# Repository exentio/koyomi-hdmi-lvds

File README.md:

# Project Koyomi - HDMI-LVDS adapter

This is part of the development of Project Koyomi, read [this blog post](https://blog.exentio.sexy/2023/12/11/project-koyomi-planning.html)
for more.  
The purpose of this adapter is to test and play around with the display of the
Vaio P before further development of the motherboard and to be used in
hand-wired builds.  

**⚠️ WARNING: at the moment of writing, the board hasn't been tested.**  

The board uses Texas Instruments' SN75LVDS83B LVDS transmitter and TFP401 DVI
receiver to send video out to the display.  

The display connector is made by I-PEX, and the model numbers are
`20374-030E-31`/`20374-R30E-31`, they're the same but the 0 variant seems to be
more common.  
The display, in my case a LT080EE04100 by Toshiba (it should be the same for
all Vaio Ps), has no backlight driver, and for that the backlight pins are
broken out, allowing testing of different drivers.  

Reference timings from [this post on patters' blog](https://pcloadletter.co.uk/2012/07/06/iemgd-for-vaio-p/),
huge thank you!  

Pixel clock in Hz: `83600000`  
Horizontal active pixels: `1600`  
Horizontal front porch: `32`  
Horizontal sync time: `65`  
Horizontal back porch: `97`  
Horizontal blank time (HFP+HST+HBP): `194`  
Vertical active pixels: `768`  
Vertical front porch: `1`  
Vertical sync time: `1`  
Vertical back porch: `8`  
Vertical blank time (VFP+VST+VBP): `10`  

---

### Forking guidelines
I hope that this design will inspire people to work on similar projects, and
that they'll be used as references to learn how to work on similar projects!  
If you want to make any contribution, you're welcome to fork and send a pull
request, as long as LLMs are not directly involved and you understand your
changes: please refer to (HUMAN.md)[https://github.com/exentio/koyomi-hdmi-lvds/blob/main/HUMAN.md], thank you.  

You're also welcome to make changes to any part of this project to implement
different design choices, without having to send a pull request; however, if
your fork takes a completely different direction from Koyomi and breaks
compatibility, I kindly ask you to drop the name "Koyomi" from your project.
Please also remove every art on the PCB, if possible (wouldn't make sense to
have my face on a completely different project anyway).  
This can't and won't be enforced, so I'm just asking informally to please
respect this request, if you want to use my designs.  

### Commercial use
I purposely decided to allow commercial use for this project for two reasons: I
would be happy if modernized Vaio Ps and Koyomi were to be used in professional
contexts, and to let people distribute PCBs so everyone can build their own,
without having to sell parts myself, which is not something I can handle.  

If you plan to sell boards and parts, I only have these simple requests:  
- Please make them reasonably affordable and don't mark them up absurdly, I
want this project to be approachable from every point of view.  
- If you're profiting from reselling my designs, please donate something back
to the people who made the designs you're selling.  
- Don't remove any drawings/art on the PCBs, but you're allowed to add your own.  

None of these can and will be enforced, so I'm just asking you to respect the
time and hard work the other contributors and I have poured into designing
Koyomi.

---

Huge thanks to Arya ([@CRImier](https://github.com/CRImier)) for her help during most phases of the design!

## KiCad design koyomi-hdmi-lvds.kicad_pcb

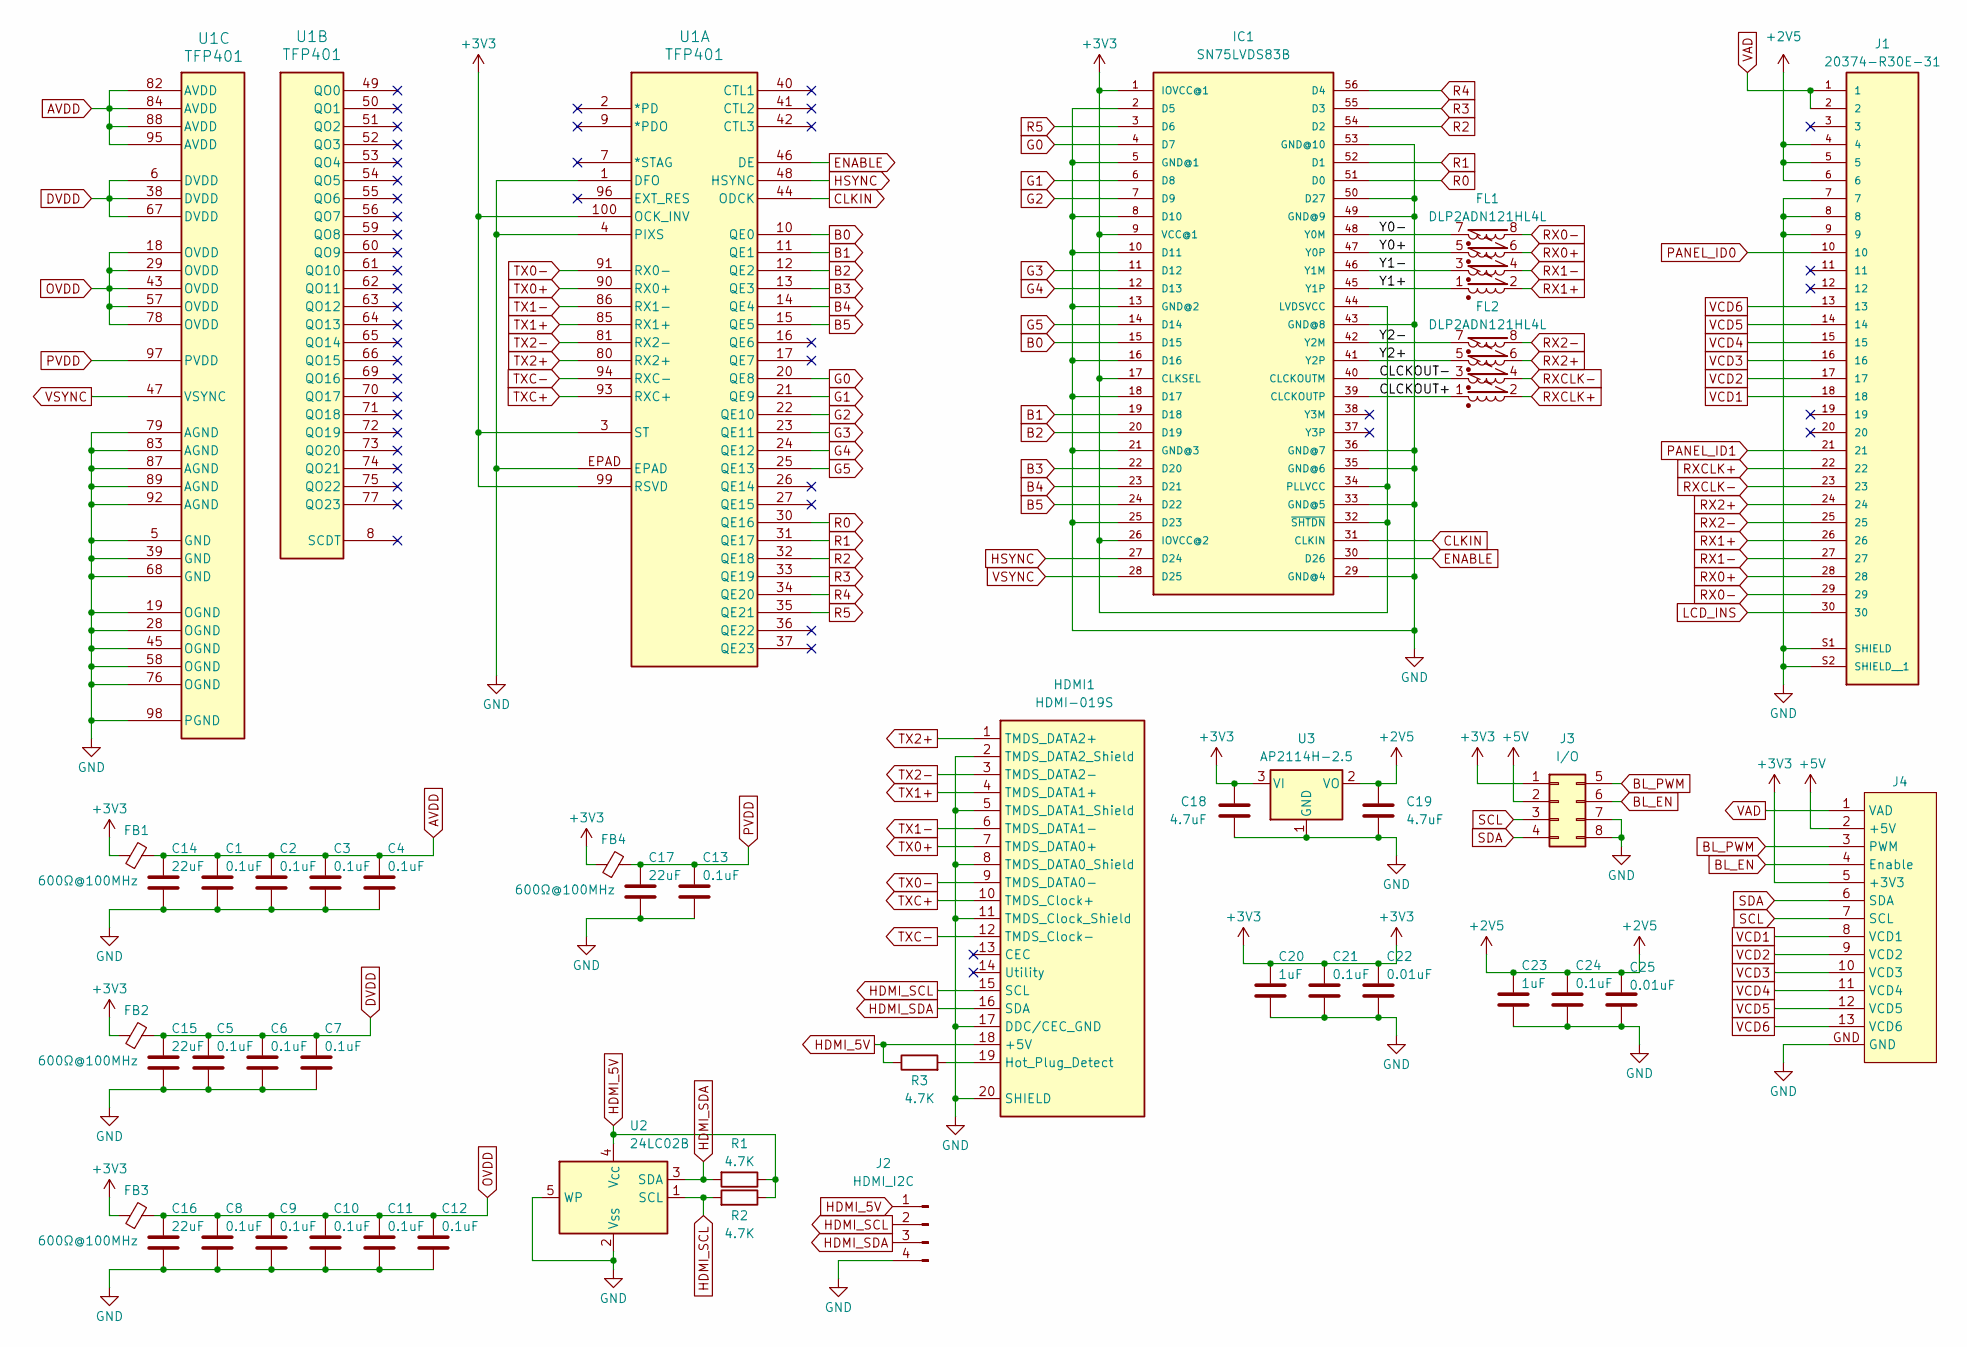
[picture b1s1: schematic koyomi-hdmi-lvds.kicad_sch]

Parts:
C1, C2, C3, C4, C5, C6, C7, C8, C9, C10, C11, C12, C13, C21, C24: 0.1uF; C_0603_1608Metric_Pad1.08x0.95mm_HandSolder; LCSC C1591
C14, C15, C16, C17: 22uF; C_0603_1608Metric_Pad1.08x0.95mm_HandSolder; LCSC C86295
C18, C19: 4.7uF; C_0603_1608Metric_Pad1.08x0.95mm_HandSolder; LCSC C1705
C20, C23: 1uF; C_0603_1608Metric_Pad1.08x0.95mm_HandSolder; LCSC C1592
C22, C25: 0.01uF; C_0603_1608Metric_Pad1.08x0.95mm_HandSolder; LCSC C1589
FB1, FB2, FB3, FB4: 600Ω@100MHz; L_0603_1608Metric_Pad1.05x0.95mm_HandSolder; LCSC C19330
FL1, FL2: DLP2ADN121HL4L; Murata_DLP2ADN121HL4L; LCSC C91592
HDMI1: HDMI-019S; HDMI-SMD_HDMI-019S; LCSC C111617
IC1: SN75LVDS83B; TSSOP56; DIGIKEY 296-24529-6-ND
J1: 20374-R30E-31; I-PEX_20374-R30E-31; PARTREV 24
J2: HDMI_I2C; PinHeader_1x04_P2.54mm_Vertical
J3: I/O; PinHeader_2x04_P2.54mm_Vertical
J4: koyomi_bl_test_driver
R1, R2, R3: 4.7K; R_0603_1608Metric_Pad0.98x0.95mm_HandSolder; LCSC C844791
U1: TFP401; LCSC C962083
U2: 24LC02B; SOT-23-5_HandSoldering; LCSC C2987265
U3: AP2114H-2.5; SOT-223-3_TabPin2; LCSC C460313

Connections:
+2V5: C19.1, C23.1, C24.1, C25.1, J1.4, J1.5, J1.6, U3.2 (VO)
+3V3: C18.1, C20.1, C21.1, C22.1, FB1.1, FB2.1, FB3.1, FB4.1, IC1.1 (IOVCC@1), IC1.9 (VCC@1), IC1.17 (CLKSEL), IC1.26 (IOVCC@2), IC1.32 (~SHTDN), IC1.34 (PLLVCC), IC1.44 (LVDSVCC), J3.1, J4.5 (+3V3), U1.3 (ST), U1.99 (RSVD), U1.100 (OCK_INV), U3.3 (VI)
+5V: J3.2, J4.2 (+5V)
/CLCKOUT+: FL2.1, IC1.39 (CLCKOUTP)
/CLCKOUT-: FL2.3, IC1.40 (CLCKOUTM)
/Y0+: FL1.5, IC1.47 (Y0P)
/Y0-: FL1.7, IC1.48 (Y0M)
/Y1+: FL1.1, IC1.45 (Y1P)
/Y1-: FL1.3, IC1.46 (Y1M)
/Y2+: FL2.5, IC1.41 (Y2P)
/Y2-: FL2.7, IC1.42 (Y2M)
AVDD: C1.1, C2.1, C3.1, C4.1, C14.1, FB1.2, U1.82 (AVDD), U1.84 (AVDD), U1.88 (AVDD), U1.95 (AVDD)
B0: IC1.15 (D15), U1.10 (QE0)
B1: IC1.19 (D18), U1.11 (QE1)
B2: IC1.20 (D19), U1.12 (QE2)
B3: IC1.22 (D20), U1.13 (QE3)
B4: IC1.23 (D21), U1.14 (QE4)
B5: IC1.24 (D22), U1.15 (QE5)
BL_EN: J3.6, J4.4 (Enable)
BL_PWM: J3.5, J4.3 (PWM)
CLKIN: IC1.31 (CLKIN), U1.44 (ODCK)
DVDD: C5.1, C6.1, C7.1, C15.1, FB2.2, U1.6 (DVDD), U1.38 (DVDD), U1.67 (DVDD)
ENABLE: IC1.30 (D26), U1.46 (DE)
G0: IC1.4 (D7), U1.20 (QE8)
G1: IC1.6 (D8), U1.21 (QE9)
G2: IC1.7 (D9), U1.22 (QE10)
G3: IC1.11 (D12), U1.23 (QE11)
G4: IC1.12 (D13), U1.24 (QE12)
G5: IC1.14 (D14), U1.25 (QE13)
GND: C1.2, C2.2, C3.2, C4.2, C5.2, C6.2, C7.2, C8.2, C9.2, C10.2, C11.2, C12.2, C13.2, C14.2, C15.2, C16.2, C17.2, C18.2, C19.2, C20.2, C21.2, C22.2, C23.2, C24.2, C25.2, HDMI1.2 (TMDS_DATA2_Shield), HDMI1.5 (TMDS_DATA1_Shield), HDMI1.8 (TMDS_DATA0_Shield), HDMI1.11 (TMDS_Clock_Shield), HDMI1.17 (DDC/CEC_GND), HDMI1.20 (SHIELD), IC1.2 (D5), IC1.5 (GND@1), IC1.8 (D10), IC1.10 (D11), IC1.13 (GND@2), IC1.16 (D16), IC1.18 (D17), IC1.21 (GND@3), IC1.25 (D23), IC1.29 (GND@4), IC1.33 (GND@5), IC1.35 (GND@6), IC1.36 (GND@7), IC1.43 (GND@8), IC1.49 (GND@9), IC1.50 (D27), IC1.53 (GND@10), J1.7, J1.8, J1.9, J1.S1 (SHIELD), J1.S2 (SHIELD__1), J2.4, J3.7, J3.8, J4.GND, U1.1 (DFO), U1.4 (PIXS), U1.5 (GND), U1.19 (OGND), U1.28 (OGND), U1.39 (GND), U1.45 (OGND), U1.58 (OGND), U1.68 (GND), U1.76 (OGND), U1.79 (AGND), U1.83 (AGND), U1.87 (AGND), U1.89 (AGND), U1.92 (AGND), U1.98 (PGND), U1.EPAD, U2.2 (V_{SS}), U2.5 (WP), U3.1 (GND)
HDMI_5V: HDMI1.18 (+5V), J2.1, R1.1, R2.1, R3.1, U2.4 (V_{CC})
HDMI_SCL: HDMI1.15 (SCL), J2.2, R2.2, U2.1 (SCL)
HDMI_SDA: HDMI1.16 (SDA), J2.3, R1.2, U2.3 (SDA)
HSYNC: IC1.27 (D24), U1.48 (HSYNC)
LCD_INS: J1.30
unnamed: HDMI1.19 (Hot_Plug_Detect), R3.2
OVDD: C8.1, C9.1, C10.1, C11.1, C12.1, C16.1, FB3.2, U1.18 (OVDD), U1.29 (OVDD), U1.43 (OVDD), U1.57 (OVDD), U1.78 (OVDD)
PANEL_ID0: J1.10
PANEL_ID1: J1.21
PVDD: C13.1, C17.1, FB4.2, U1.97 (PVDD)
R0: IC1.51 (D0), U1.30 (QE16)
R1: IC1.52 (D1), U1.31 (QE17)
R2: IC1.54 (D2), U1.32 (QE18)
R3: IC1.55 (D3), U1.33 (QE19)
R4: IC1.56 (D4), U1.34 (QE20)
R5: IC1.3 (D6), U1.35 (QE21)
RX0+: FL1.6, J1.28
RX0-: FL1.8, J1.29
RX1+: FL1.2, J1.26
RX1-: FL1.4, J1.27
RX2+: FL2.6, J1.24
RX2-: FL2.8, J1.25
RXCLK+: FL2.2, J1.22
RXCLK-: FL2.4, J1.23
SCL: J3.3, J4.7 (SCL)
SDA: J3.4, J4.6 (SDA)
TX0+: HDMI1.7 (TMDS_DATA0+), U1.90 (RX0+)
TX0-: HDMI1.9 (TMDS_DATA0-), U1.91 (RX0-)
TX1+: HDMI1.4 (TMDS_DATA1+), U1.85 (RX1+)
TX1-: HDMI1.6 (TMDS_DATA1-), U1.86 (RX1-)
TX2+: HDMI1.1 (TMDS_DATA2+), U1.80 (RX2+)
TX2-: HDMI1.3 (TMDS_DATA2-), U1.81 (RX2-)
TXC+: HDMI1.10 (TMDS_Clock+), U1.93 (RXC+)
TXC-: HDMI1.12 (TMDS_Clock-), U1.94 (RXC-)
VAD: J1.1, J1.2, J4.1 (VAD)
VCD1: J1.18, J4.8 (VCD1)
VCD2: J1.17, J4.9 (VCD2)
VCD3: J1.16, J4.10 (VCD3)
VCD4: J1.15, J4.11 (VCD4)
VCD5: J1.14, J4.12 (VCD5)
VCD6: J1.13, J4.13 (VCD6)
VSYNC: IC1.28 (D25), U1.47 (VSYNC)

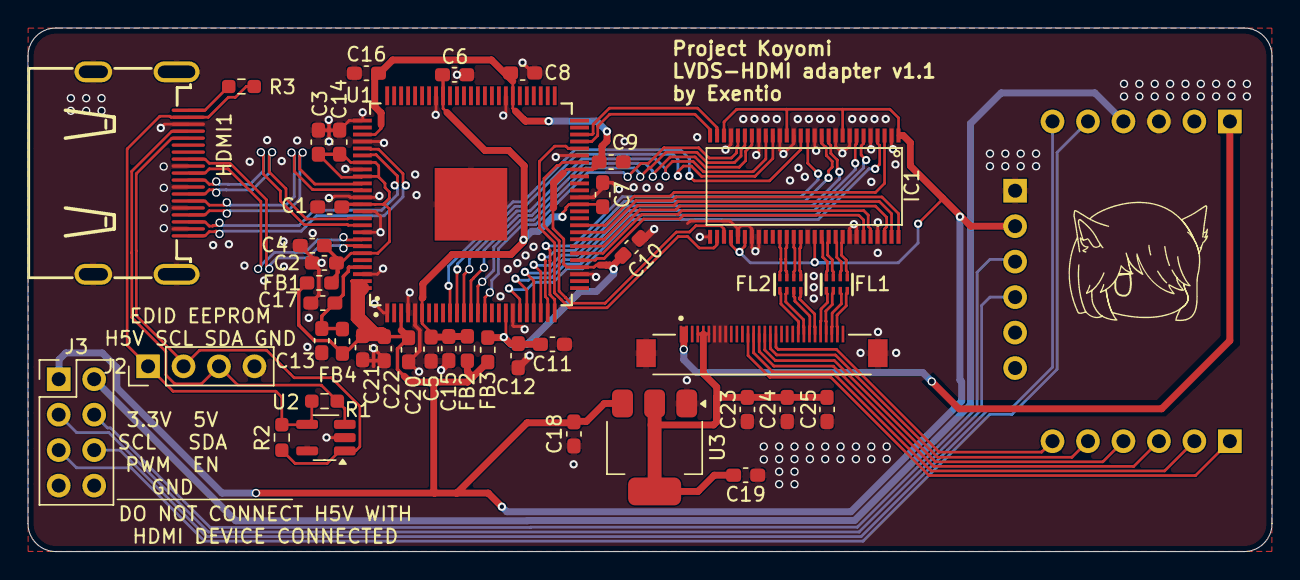
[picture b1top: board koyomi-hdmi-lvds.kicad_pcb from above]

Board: 2 copper layers, 89.1 x 37.5 mm, 43 parts (0 on the bottom side), 69 nets.

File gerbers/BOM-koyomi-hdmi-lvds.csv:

Comment,Designator,Footprint,LCSC,Quantity
0.01uF,"C22,C25",C_0603_1608Metric_Pad1.08x0.95mm_HandSolder,C1589,2
0.1uF,"C1,C10,C11,C12,C13,C2,C21,C24,C3,C4,C5,C6,C7,C8,C9",C_0603_1608Metric_Pad1.08x0.95mm_HandSolder,C1591,15
1uF,"C20,C23",C_0603_1608Metric_Pad1.08x0.95mm_HandSolder,C1592,2
22uF,"C14,C15,C16,C17",C_0603_1608Metric_Pad1.08x0.95mm_HandSolder,C86295,4
24LC02B,U2,SOT-23-5_HandSoldering,C2987265,1
4.7K,"R1,R2,R3",R_0603_1608Metric_Pad0.98x0.95mm_HandSolder,C844791,3
4.7uF,"C18,C19",C_0603_1608Metric_Pad1.08x0.95mm_HandSolder,C1705,2
600Ω@100MHz,"FB1,FB2,FB3,FB4",L_0603_1608Metric_Pad1.05x0.95mm_HandSolder,C19330,4
AP2114H-2.5,U3,SOT-223-3_TabPin2,C460313,1
DLP2ADN121HL4L,"FL1,FL2",Murata_DLP2ADN121HL4L,C91592,2
HDMI-019S,HDMI1,HDMI-SMD_HDMI-019S,C111617,1
PZP100_5P2X5P2,U1,TFP401,C962083,1
SN75LVDS83B,IC1,TSSOP56,C35164,1
20374-R30E-31,J1,I-PEX_20374-R30E-31,,1

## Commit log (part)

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2024-05-15 Add license
2024-06-19 Rerouting by @CRImier
2024-07-21 JLCPCB files update
2024-08-01 Changed PCB art to simple silkscreen lines
2024-08-03 Update gerbers to reflect recent changes
2024-12-27 Fix JLCPCB rotations
2024-12-28 Readme change
